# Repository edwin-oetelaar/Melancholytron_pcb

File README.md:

# Melancholytron_pcb

* Combines Teensy 3.2 with audio board and MIDI interface
* Kicad latest nightly for development

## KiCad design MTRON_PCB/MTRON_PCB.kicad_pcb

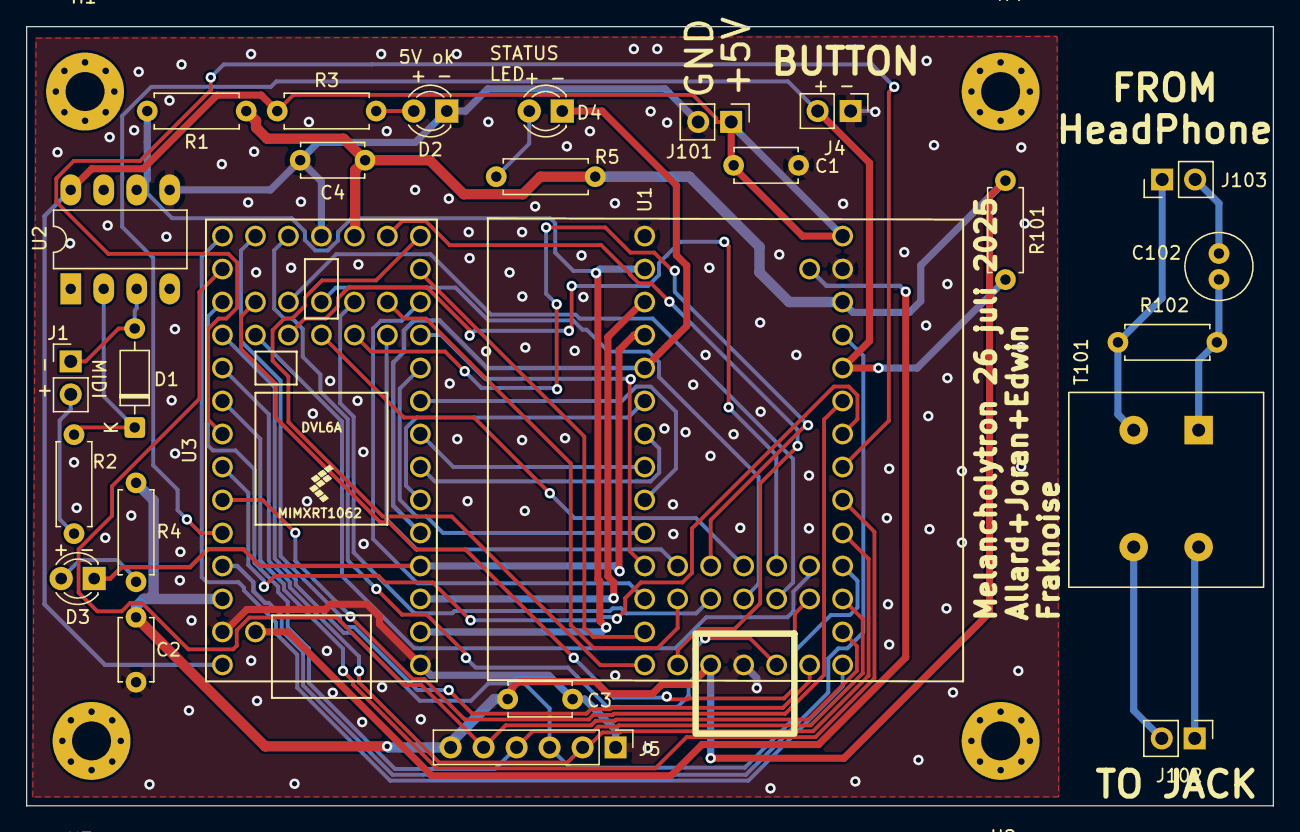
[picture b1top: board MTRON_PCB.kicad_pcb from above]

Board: 2 copper layers, 96.0 x 60.0 mm, 30 parts (0 on the bottom side), 52 nets.

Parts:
C1, C2, C3, C4: 100n; C_Disc_D4.7mm_W2.5mm_P5.00mm
C102: C_Small; C_Radial_D5.0mm_H11.0mm_P2.00mm
D1: 1N4148; D_DO-35_SOD27_P7.62mm_Horizontal
D2, D3, D4: LED; LED_D3.0mm
H1, H2, H3, H4: MountingHole_Pad; MountingHole_3mm_Pad_Via
J1, J4, J101, J102, J103: Conn_01x02; PinHeader_1x02_P2.54mm_Vertical
J5: Conn_01x06; PinHeader_1x06_P2.54mm_Vertical
R1, R3, R4, R5, R101: 470R; R_Axial_DIN0207_L6.3mm_D2.5mm_P7.62mm_Horizontal
R2: 220R; R_Axial_DIN0207_L6.3mm_D2.5mm_P7.62mm_Horizontal
R102: 10K; R_Axial_DIN0207_L6.3mm_D2.5mm_P7.62mm_Horizontal
T101: EL-11 (tinytronics); Transformer_EL-11-tinytronics
U1: Teensy4.0; Teensy40_audio_shield
U2: 6N138; DIP-8_W7.62mm_LongPads
U3: Teensy4.0; Teensy40

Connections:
GROUND: C1.2, C2.2, C3.2, C4.2, D2.1 (K), J4.1, J5.1, J101.2, U1.1 (GND), U1.17 (GND), U1.32 (GND), U2.5 (GND), U3.1 (GND), U3.17 (GND), U3.32 (GND)
LD1: D3.1 (K), U1.4 (2_OUT2), U3.4 (2_OUT2)
LD2: D4.1 (K), U1.5 (3_LRCLK2), U3.5 (3_LRCLK2)
unnamed: C102.2, R102.1, T101.1
unnamed: D1.2 (A), J1.1, U2.3 (C2)
unnamed: D1.1 (K), R2.2, U2.2 (C1)
unnamed: D2.2 (A), R3.2
unnamed: D3.2 (A), R4.2
unnamed: D4.2 (A), R5.2
unnamed: J1.2, R2.1
unnamed: J102.1, T101.4
unnamed: J102.2, T101.3
unnamed: J103.1, R102.2, T101.2
unnamed: C102.1, J103.2
P2: R1.2, U1.2 (0_RX1_CRX2_CS1), U2.6 (VO2), U3.2 (0_RX1_CRX2_CS1)
P3: U1.3 (1_TX1_CTX2_MISO1), U3.3 (1_TX1_CTX2_MISO1)
P6: U1.6 (4_BCLK2), U3.6 (4_BCLK2)
P7: U1.7 (5_IN2), U3.7 (5_IN2)
P8: U1.8 (6_OUT1D), U3.8 (6_OUT1D)
P9: U1.9 (7_RX2_OUT1A), U3.9 (7_RX2_OUT1A)
P10: U1.10 (8_TX2_IN1), U3.10 (8_TX2_IN1)
P11: U1.11 (9_OUT1C), U3.11 (9_OUT1C)
P12: U1.12 (10_CS_MQSR), U3.12 (10_CS_MQSR)
P13: U1.13 (11_MOSI_CTX1), U3.13 (11_MOSI_CTX1)
P14: U1.14 (12_MISO_MQSL), U3.14 (12_MISO_MQSL)
P15: U1.15 (VBAT), U3.15 (VBAT)
P16: C2.1, C3.1, C4.1, J5.6, R1.1, R4.1, R5.1, R101.2, U1.16 (3V3), U1.31 (3V3), U3.16 (3V3), U3.31 (3V3)
P18: U1.18 (PROGRAM), U3.18 (PROGRAM)
P19: U1.19 (ON_OFF), U3.19 (ON_OFF)
P20: U1.20 (13_SCK_CRX1_LED), U3.20 (13_SCK_CRX1_LED)
P21: J5.5, U1.21 (14_A0_TX3_SPDIF_OUT), U3.21 (14_A0_TX3_SPDIF_OUT)
P22: J5.4, U1.22 (15_A1_RX3_SPDIF_IN), U3.22 (15_A1_RX3_SPDIF_IN)
P23: J5.3, U1.23 (16_A2_RX4_SCL1), U3.23 (16_A2_RX4_SCL1)
P24: J5.2, U1.24 (17_A3_TX4_SDA1), U3.24 (17_A3_TX4_SDA1)
P25: U1.25 (18_A4_SDA0), U3.25 (18_A4_SDA0)
P26: U1.26 (19_A5_SCL0), U3.26 (19_A5_SCL0)
P27: U1.27 (20_A6_TX5_LRCLK1), U3.27 (20_A6_TX5_LRCLK1)
P28: U1.28 (21_A7_RX5_BCLK1), U3.28 (21_A7_RX5_BCLK1)
P29: J4.2, R101.1, U1.29 (22_A8_CTX1), U3.29 (22_A8_CTX1)
P30: U1.30 (23_A9_CRX1_MCLK1), U3.30 (23_A9_CRX1_MCLK1)
P33: C1.1, J101.1, R3.1, U1.33 (VIN), U2.8 (VCC), U3.33 (VIN)
P34: U1.34 (VUSB), U3.34 (VUSB)
P35: U1.35 (24_A10_TX6_SCL2), U3.35 (24_A10_TX6_SCL2)
P36: U1.36 (25_A11_RX6_SDA2), U3.36 (25_A11_RX6_SDA2)
P37: U1.37 (26_A12_MOSI1), U3.37 (26_A12_MOSI1)
P38: U1.38 (27_A13_SCK1), U3.38 (27_A13_SCK1)
P39: U1.39 (28_RX7), U3.39 (28_RX7)
P40: U1.40 (29_TX7), U3.40 (29_TX7)
P41: U1.41 (30_CRX3), U3.41 (30_CRX3)
P42: U1.42 (31_CTX3), U3.42 (31_CTX3)
P43: U1.43 (32_OUT1B), U3.43 (32_OUT1B)
P44: U1.44 (33_MCLK2), U3.44 (33_MCLK2)

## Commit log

2022-06-06 initial file
2022-06-12 Added circuit board design. Ordered PCB. Files up to date with ordered pcb.
2025-04-08 nieuwe versie, veel verwijdered, in productie 8 april 2025
2025-04-08 update design files, new version has less parts
2025-05-31 nieuwe versie met alles THT en pull up voor switch. connector voor power. flip van linker device orientatie
2025-07-26 new version, includes fix for 3v3, audio transformer, logo, based on new findings.
2025-08-17 Create RPI-pico2-midicontroller.md
    eerste concept
